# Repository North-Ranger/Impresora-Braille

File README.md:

# Impresora-Braille
BrailleDotUP – Impresora Braille de Bajo Costo

Este repositorio contiene el desarrollo completo del proyecto BrailleDotUP, una impresora Braille de bajo costo diseñada como trabajo de grado para el Instituto Nacional para Ciegos (INCI). Incluye diseños mecánicos, archivos de manufactura, esquemas electrónicos, firmware y software de comunicación.

El objetivo del proyecto es ofrecer una alternativa asequible frente a las impresoras Braille comerciales, cuyo costo suele superar los 5.000 USD, limitando el acceso a materiales accesibles en instituciones educativas y comunidades con recursos limitados.

Contenido del Repositorio
---------------------------------------------------------------
Hardware
---------------------------------------------------------------
Contiene los archivos necesarios para fabricar la impresora:

Modelos 3D en formato STL

Archivos de corte láser (DXF, SVG)

Planos mecanizados (CNC)

Planos completos en PDF

👉 Ver carpeta: /Hardware/

Electrónica
---------------------------------------------------------------
Incluye:

Esquemáticos del sistema basado en Arduino Mega 2560 + RAMPS 1.4

PCB del circuito de solenoides con TIP122

Fichas técnicas de componentes clave

👉 Ver carpeta: /Electrónica/

Software y Firmware
---------------------------------------------------------------
Contiene:

Software AccesBrailleDotUP para comunicación y conversión a Braille

Firmware modificado de Marlin para control de motores y solenoides

Scripts auxiliares en Arduino o Python

👉 Ver carpeta: /Código/

Documentación
---------------------------------------------------------------
Incluye:

Fichas técnicas

Manual de usuario

Memoria final del proyecto

👉 Ver carpeta: /Documentación/

Requisitos para compilar y usar
Hardware
---------------------------------------------------------------
Arduino Mega 2560

RAMPS 1.4

Drivers A4988

TIP122 para solenoides

Módulo Bluetooth HC-05

Sensores mecánicos/ópticos

Motores NEMA 17

Software

Arduino IDE

Marlin Firmware

AccesBrailleDotUP (incluido en este repo)

SolidWorks (para edición CAD, no incluido)

Contacto
---------------------------------------------------------------
Para inquietudes o solicitudes de colaboración:

Nombre(s) de autores 

Jorge Daniel Rey Rios

John Alejandro Morales Useche

Correo(s)

jorge_rey@javeriana.edu.co

moralesuj@javeriana.edu.co

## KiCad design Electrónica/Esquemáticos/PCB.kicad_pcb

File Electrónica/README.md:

📌 Descripción General
-----------------------
Este directorio contiene el diseño completo del subsistema electrónico de la impresora Braille DotUP, incluyendo esquemáticos, 
PCB, listas de materiales, diagramas de conexión y documentación técnica asociada.

Este repositorio centraliza todo lo necesario para replicar, auditar o modificar el sistema electrónico del prototipo.

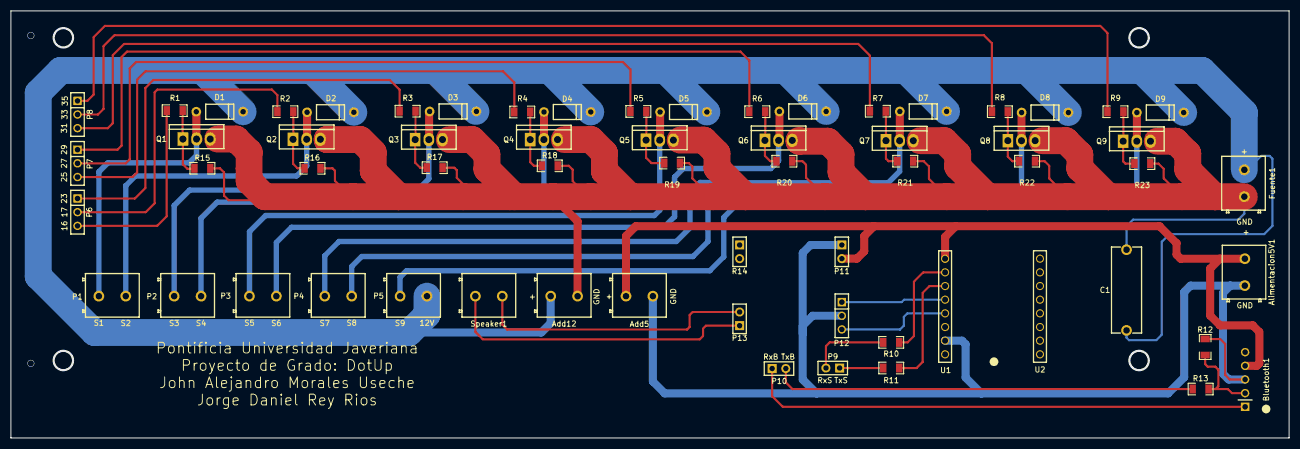
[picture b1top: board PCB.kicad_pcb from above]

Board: 2 copper layers, 237.6 x 79.4 mm, 63 parts (0 on the bottom side), 42 nets.

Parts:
Add5, Add12: WJ127-5.0-2P; CONN-TH_2P-P5.00_CPC3703CTR
Alimentacion5V1: WJ127-5.0-2P; CONN-TH_2P-P5.00_CPC3703CTR
Bluetooth1: Female header 2.54 1*5Ｐ; HDR-TH_5P-P2.54-V-F-B
C1: 1000 uF; CAP-TH_L16.0-W5.5-P15.00-D1.2
D1, D2, D3, D4, D5, D6, D7, D8, D9: 1N4001_C2456; DO-41_BD2.4-L4.7-P8.70-D0.9-RD
Fuente1: WJ127-5.0-2P; CONN-TH_2P-P5.00_CPC3703CTR
P1, P2, P3, P4, P5: WJ127-5.0-2P; CONN-TH_2P-P5.00_CPC3703CTR
P6, P7, P8, P12: Header-Female-2.54_1x3; HDR-TH_3P-P2.54-V-F
P9, P10, P11, P13: Header-Female-2.54_1x2; HDR-TH_2P-P2.54-V-F
Q1, Q2, Q3, Q4, Q5, Q6, Q7, Q8, Q9: IRLZ44NPBF; TO-220-3_L10.0-W4.5-P2.54-T
R1, R2, R3, R4, R5, R6, R7, R8, R9: 1206W4F2200T5E; R1206
R10, R11, R12: 1206W4J0102T5E; R1206
R13: RTT066800FTP; R1206
R14: Header-Female-2.54_1x2; HDR-TH_2P-P2.54-V-F
R15, R16, R17, R18, R19, R20, R21, R22, R23: 10k; R1206
Speaker1: WJ127-5.0-2P; CONN-TH_2P-P5.00_CPC3703CTR
U1, U2: HC-PM254-5.0H-1X8PZ; CONN-TH_HC-PM254-1X08-8.5HZ

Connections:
+12V: Add12.1, C1.1, D2.1 (C), D3.1 (C), D4.1 (C), D5.1 (C), D6.1 (C), D7.1 (C), D8.1 (C), D9.1 (C), Fuente1.2, P5.2
GND: Add12.2, C1.2, Fuente1.1, Q1.3 (S), Q2.3 (S), Q3.3 (S), Q4.3 (S), Q5.3 (S), Q6.3 (S), Q7.3 (S), Q8.3 (S), Q9.3 (S), R15.1, R16.1, R17.1, R18.1, R19.1, R20.1, R21.1, R22.1, R23.1
unnamed: Add5.2, Alimentacion5V1.1, Bluetooth1.3 (GND), P11.1 (-), P12.2 (GND), R12.2, U1.7 (GND)
unnamed: Bluetooth1.1 (Rx), P10.1
unnamed: Bluetooth1.2 (Tx), R12.1, R13.1
unnamed: Add5.1, Alimentacion5V1.2, Bluetooth1.4 (Vcc), P11.2 (+), U1.1 (VCC)
unnamed: D2.2 (A), P1.2, Q2.2 (D)
unnamed: D3.2 (A), P2.1, Q3.2 (D)
unnamed: D4.2 (A), P2.2, Q4.2 (D)
unnamed: D5.2 (A), P3.1, Q5.2 (D)
unnamed: D6.2 (A), P3.2, Q6.2 (D)
unnamed: D7.2 (A), P4.1, Q7.2 (D)
unnamed: D8.2 (A), P4.2, Q8.2 (D)
unnamed: D9.2 (A), P5.1, Q9.2 (D)
unnamed: P6.1, R3.1
unnamed: P6.2, R2.1
unnamed: P6.3, R1.1
unnamed: P7.1, R6.1
unnamed: P7.2, R5.1
unnamed: P7.3, R4.1
unnamed: P8.1, R9.1
unnamed: P8.2, R8.1
unnamed: P8.3, R7.1
unnamed: P9.1, R11.1
unnamed: P9.2, R10.1
unnamed: P10.2, R13.2
unnamed: P12.3 (L), U1.5 (DACL)
unnamed: P12.1 (R), U1.4 (DACR)
unnamed: P13.2 (+), Speaker1.2
unnamed: P13.1 (-), Speaker1.1
unnamed: P1.1, Q1.2 (D)
unnamed: Q1.1 (G), R1.2, R15.2
unnamed: Q2.1 (G), R2.2, R16.2
unnamed: Q3.1 (G), R3.2, R17.2
unnamed: Q4.1 (G), R4.2, R18.2
unnamed: Q5.1 (G), R5.2, R19.2
unnamed: Q6.1 (G), R6.2, R20.2
unnamed: Q7.1 (G), R7.2, R21.2
unnamed: Q8.1 (G), R8.2, R22.2
unnamed: Q9.1 (G), R9.2, R23.2
unnamed: R10.2, U1.2 (Rx)
unnamed: R11.2, U1.3 (Tx)

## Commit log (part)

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2025-11-15 Enhance README with project details and requirements
    Added detailed project description, repository contents, and requirements for the BrailleDotUP printer.
2025-11-15 Fix folder names and add author contact info
    Updated folder names to use correct capitalization and added author names and contact information.
2025-11-15 Fix typo in README.md for 'Código' folder
2025-11-15 Add authors and contact information to README
2025-11-15 Update README.md with section dividers and content
2025-11-15 Enhance README formatting and section headers
    Updated the README.md to improve formatting and structure.
2025-11-15 Add manufacturing files section for BrailleDotUP
2025-11-15 Update readme with manufacturing details for BrailleDotUP
    Added detailed manufacturing files and structure for BrailleDotUP.
2025-11-15 Rename readme.md to README.md
2025-11-15 Update README with general description
    Added general description of the electronic subsystem.
2025-11-15 Improve formatting of README description
    Formatted the description for better readability.
2025-11-15 Create Esquematicos
2025-11-15 Create Production Files
2025-11-15 Fix formatting and descriptions in README.md
    Corrected formatting and improved clarity in the README.
2025-11-15 Fix folder names and formatting in README
    Updated formatting and corrected folder names in README.
2025-11-15 Create Mecanizado CNC
2025-11-15 Create Marlin
2025-11-15 Update README with project documentation details
    Add project documentation overview and purpose
2025-11-15 Rename APU_materiales_braille (1).xlsx to APU_materiales_braille.xlsx
2025-11-15 Add README.md for BrailleDotUP project
    Added README.md with project details for BrailleDotUP software and firmware.
2025-11-15 Add sections for Costs and Test Protocol
2025-11-15 Add download link for AccesBrailleDotUp
2025-11-15 Create Link Descarga
2025-11-15 Rename Link Descarga to MarlinDotUp
